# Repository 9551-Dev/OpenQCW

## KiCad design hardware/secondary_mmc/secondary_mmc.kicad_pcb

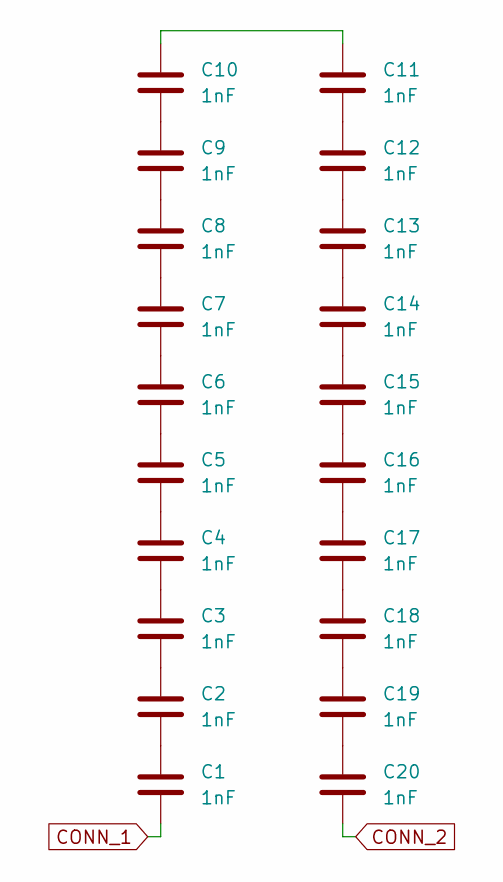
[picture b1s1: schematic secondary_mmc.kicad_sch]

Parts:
C1, C2, C3, C4, C5, C6, C7, C8, C9, C10, C11, C12, C13, C14, C15, C16, C17, C18, C19, C20: 1nF; C_1812_4532Metric_Pad1.57x3.40mm_HandSolder

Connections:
CONN_1: C1.1
CONN_2: C20.2
unnamed: C1.2, C2.1
unnamed: C2.2, C3.1
unnamed: C3.2, C4.1
unnamed: C4.2, C5.1
unnamed: C5.2, C6.1
unnamed: C6.2, C7.1
unnamed: C7.2, C8.1
unnamed: C8.2, C9.1
unnamed: C9.2, C10.1
unnamed: C10.2, C11.1
unnamed: C11.2, C12.1
unnamed: C12.2, C13.1
unnamed: C13.2, C14.1
unnamed: C14.2, C15.1
unnamed: C15.2, C16.1
unnamed: C16.2, C17.1
unnamed: C17.2, C18.1
unnamed: C18.2, C19.1
unnamed: C19.2, C20.1

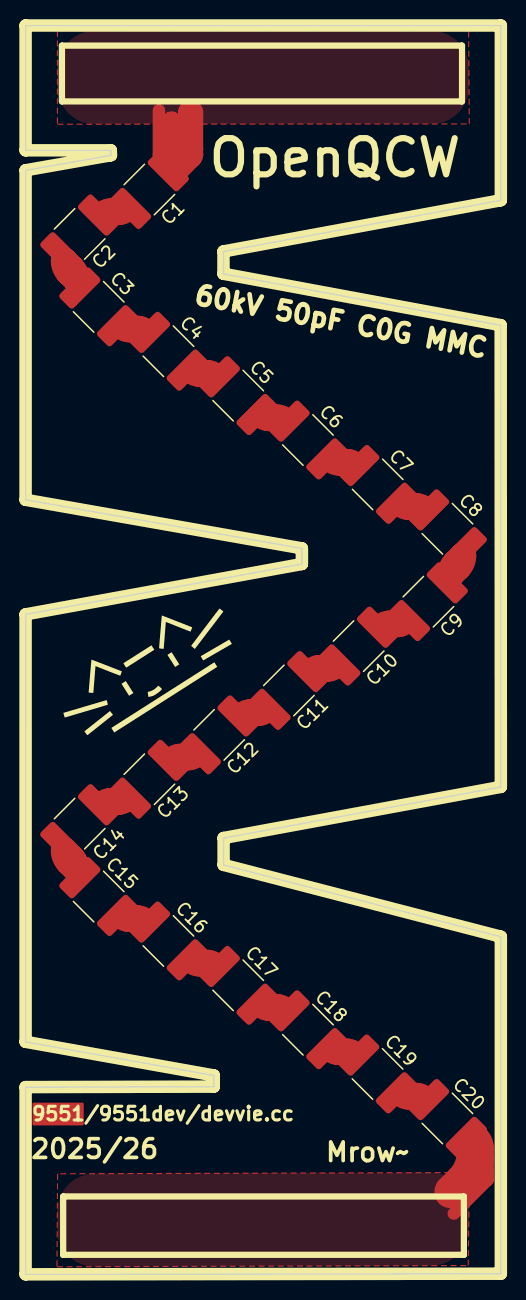
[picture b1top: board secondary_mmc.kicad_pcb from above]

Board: 2 copper layers, 38.1 x 100.1 mm, 20 parts (0 on the bottom side), 19 nets.

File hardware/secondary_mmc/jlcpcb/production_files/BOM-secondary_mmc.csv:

Comment,Designator,Footprint,LCSC,Quantity
1nF,"C1,C10,C11,C12,C13,C14,C15,C16,C17,C18,C19,C2,C20,C3,C4,C5,C6,C7,C8,C9",C_1812_4532Metric_Pad1.57x3.40mm_HandSolder,C692320,20

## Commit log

2025-12-19 init
2025-12-19 change readme
2025-12-19 add gitkeeps
2025-12-21 add halt module
2025-12-21 Fix .gitignore
2025-12-21 fix .gitkeep
2025-12-21 Add gitignore
2025-12-22 add progress on main drive controller and switch to hiearchical labels
2026-01-04 update right about freaking everything
2026-01-06 idk if i changed anything
2026-02-09 idk some changes
2026-03-02 completed-ish inverter board, probably not, but anyway
2026-03-04 minor changes
